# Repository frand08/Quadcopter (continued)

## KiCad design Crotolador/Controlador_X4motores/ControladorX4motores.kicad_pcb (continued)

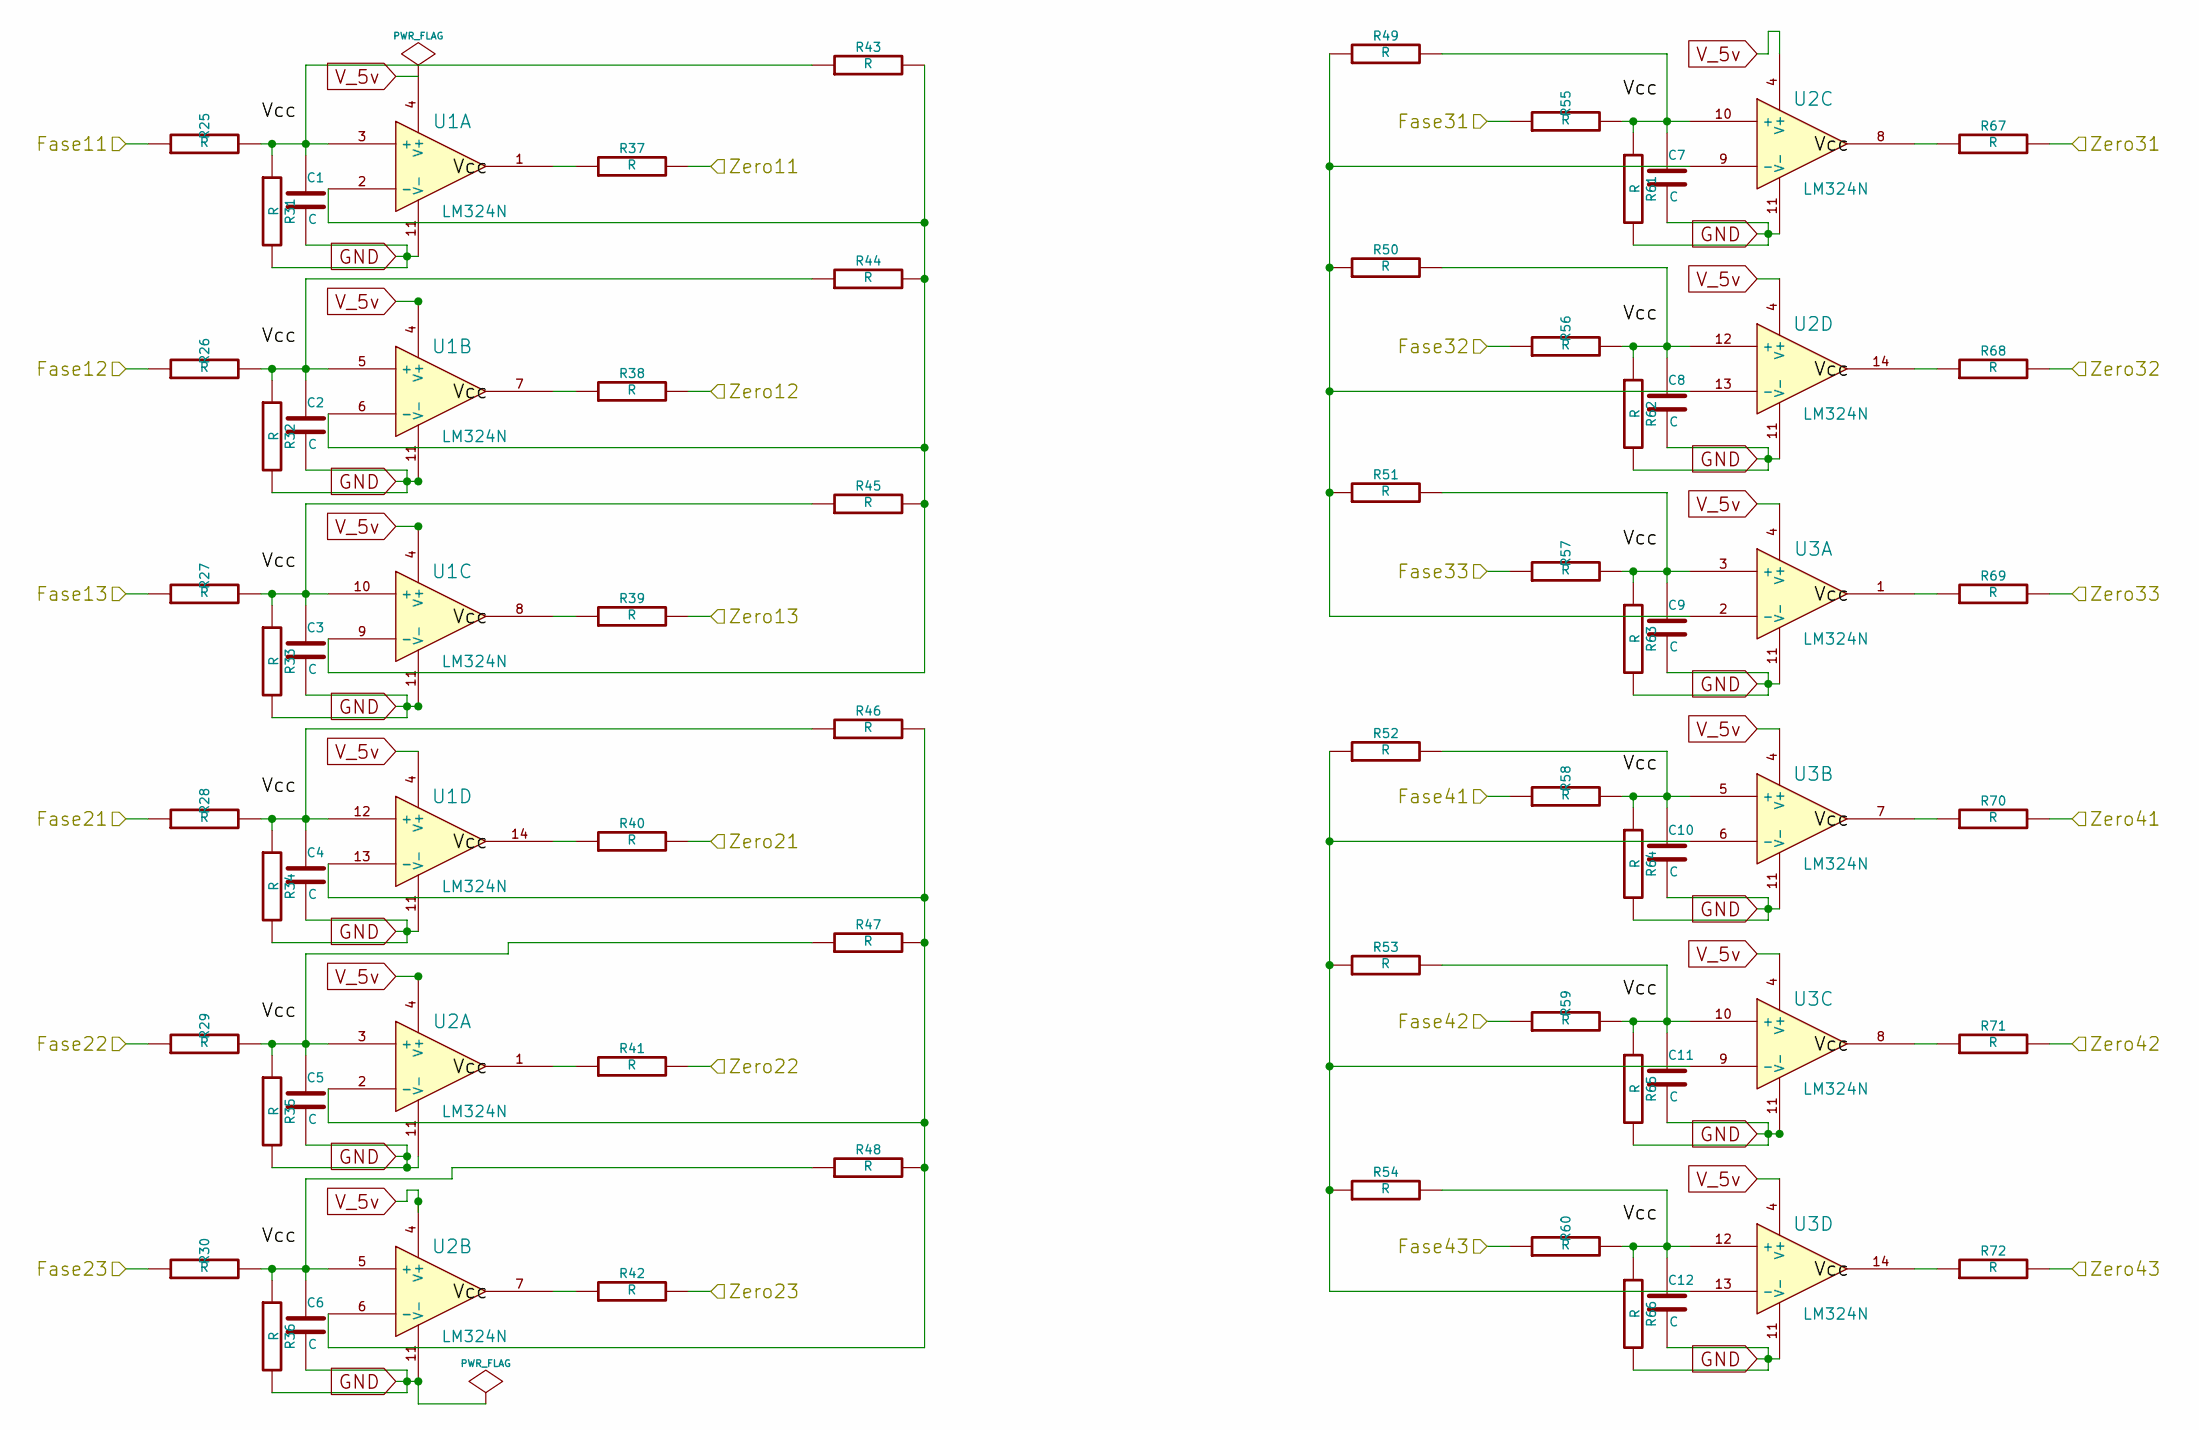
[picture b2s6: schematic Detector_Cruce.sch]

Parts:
C1, C2, C3, C4, C5, C6, C7, C8, C9, C10, C11, C12: C
R25, R26, R27, R28, R29, R30, R31, R32, R33, R34, R35, R36, R37, R38, R39, R40, R41, R42, R43, R44, R45, R46, R47, R48, R49, R50, R51, R52, R53, R54, R55, R56, R57, R58, R59, R60, R61, R62, R63, R64, R65, R66, R67, R68, R69, R70, R71, R72: R
U1, U2, U3: LM324N

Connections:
/Detector_Cruce/Fase12: R26.1; also elsewhere on the board
/Detector_Cruce/Fase13: R27.1; also elsewhere on the board
/Detector_Cruce/Fase23: R30.1; also elsewhere on the board
/Detector_Cruce/Zero11: R37.2; also elsewhere on the board
/Detector_Cruce/Zero12: R38.2; also elsewhere on the board
/Detector_Cruce/Zero13: R39.2; also elsewhere on the board
/Detector_Cruce/Zero21: R40.2; also elsewhere on the board
/Detector_Cruce/Zero22: R41.2; also elsewhere on the board
/Detector_Cruce/Zero23: R42.2; also elsewhere on the board
/Detector_Cruce/Zero31: R67.2; also elsewhere on the board
/Detector_Cruce/Zero32: R68.2; also elsewhere on the board
/Detector_Cruce/Zero33: R69.2; also elsewhere on the board
/Detector_Cruce/Zero41: R70.2; also elsewhere on the board
/Detector_Cruce/Zero42: R71.2; also elsewhere on the board
/Detector_Cruce/Zero43: R72.2; also elsewhere on the board
/MOSFET_Potencia1/Fase1: R25.1; also elsewhere on the board
/MOSFET_Potencia2/Fase1: R28.1; also elsewhere on the board
/MOSFET_Potencia2/Fase2: R29.1; also elsewhere on the board
/MOSFET_Potencia3/Fase1: R55.1; also elsewhere on the board
/MOSFET_Potencia3/Fase2: R56.1; also elsewhere on the board
/MOSFET_Potencia3/Fase3: R57.1; also elsewhere on the board
/MOSFET_Potencia4/Fase1: R58.1; also elsewhere on the board
/MOSFET_Potencia4/Fase2: R59.1; also elsewhere on the board
/MOSFET_Potencia4/Fase3: R60.1; also elsewhere on the board
GND: C1.2, C2.2, C3.2, C4.2, C5.2, C6.2, C7.2, C8.2, C9.2, C10.2, C11.2, C12.2, R31.2, R32.2, R33.2, R34.2, R35.2, R36.2, R61.2, R62.2, R63.2, R64.2, R65.2, R66.2, U1.11 (V-), U2.11 (V-), U3.11 (V-); also elsewhere on the board
unnamed: R71.1, U3.8
unnamed: R72.1, U3.14
unnamed: C12.1, R54.2, R60.2, R66.1, U3.12 (+)
unnamed: R52.1, R53.1, R54.1, U3.6 (-), U3.9 (-), U3.13 (-)
unnamed: R70.1, U3.7
unnamed: C1.1, R25.2, R31.1, R43.1, U1.3 (+)
unnamed: R43.2, R44.2, R45.2, U1.2 (-), U1.6 (-), U1.9 (-)
unnamed: R40.1, U1.14
unnamed: R46.2, R47.2, R48.2, U1.13 (-), U2.2 (-), U2.6 (-)
unnamed: R41.1, U2.1
unnamed: R38.1, U1.7
unnamed: R39.1, U1.8
unnamed: R68.1, U2.14
unnamed: R69.1, U3.1
unnamed: R42.1, U2.7
unnamed: R67.1, U2.8
unnamed: R49.1, R50.1, R51.1, U2.9 (-), U2.13 (-), U3.2 (-)
unnamed: C4.1, R28.2, R34.1, R46.1, U1.12 (+)
unnamed: C5.1, R29.2, R35.1, R47.1, U2.3 (+)
unnamed: C6.1, R30.2, R36.1, R48.1, U2.5 (+)
unnamed: R37.1, U1.1
unnamed: C2.1, R26.2, R32.1, R44.1, U1.5 (+)
unnamed: C3.1, R27.2, R33.1, R45.1, U1.10 (+)
unnamed: C10.1, R52.2, R58.2, R64.1, U3.5 (+)
unnamed: C11.1, R53.2, R59.2, R65.1, U3.10 (+)
unnamed: C7.1, R49.2, R55.2, R61.1, U2.10 (+)
unnamed: C8.1, R50.2, R56.2, R62.1, U2.12 (+)
unnamed: C9.1, R51.2, R57.2, R63.1, U3.3 (+)
V_5v: U1.4 (V+), U2.4 (V+), U3.4 (V+); also elsewhere on the board

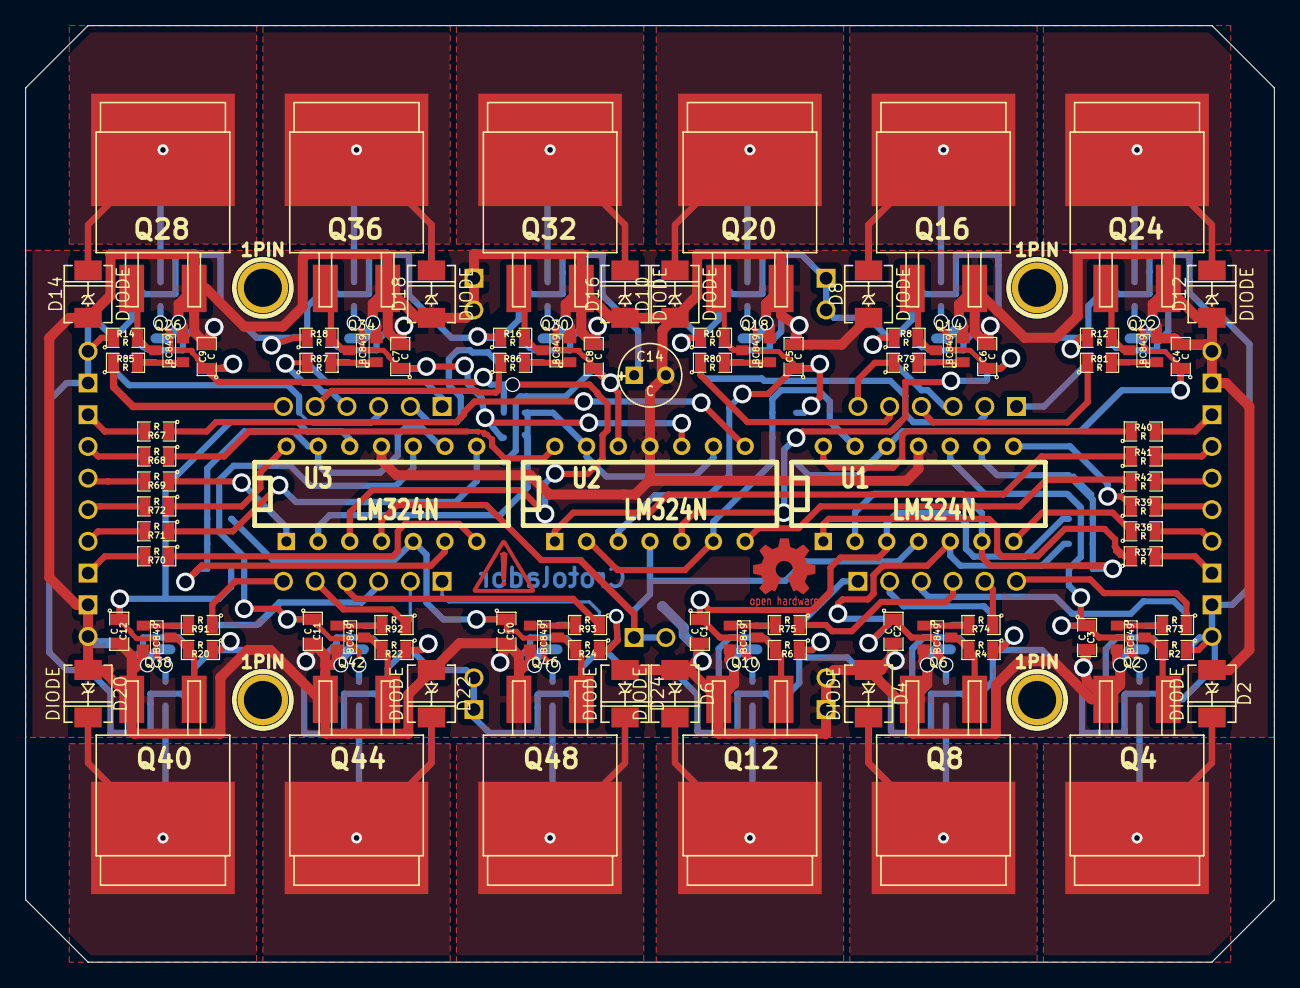
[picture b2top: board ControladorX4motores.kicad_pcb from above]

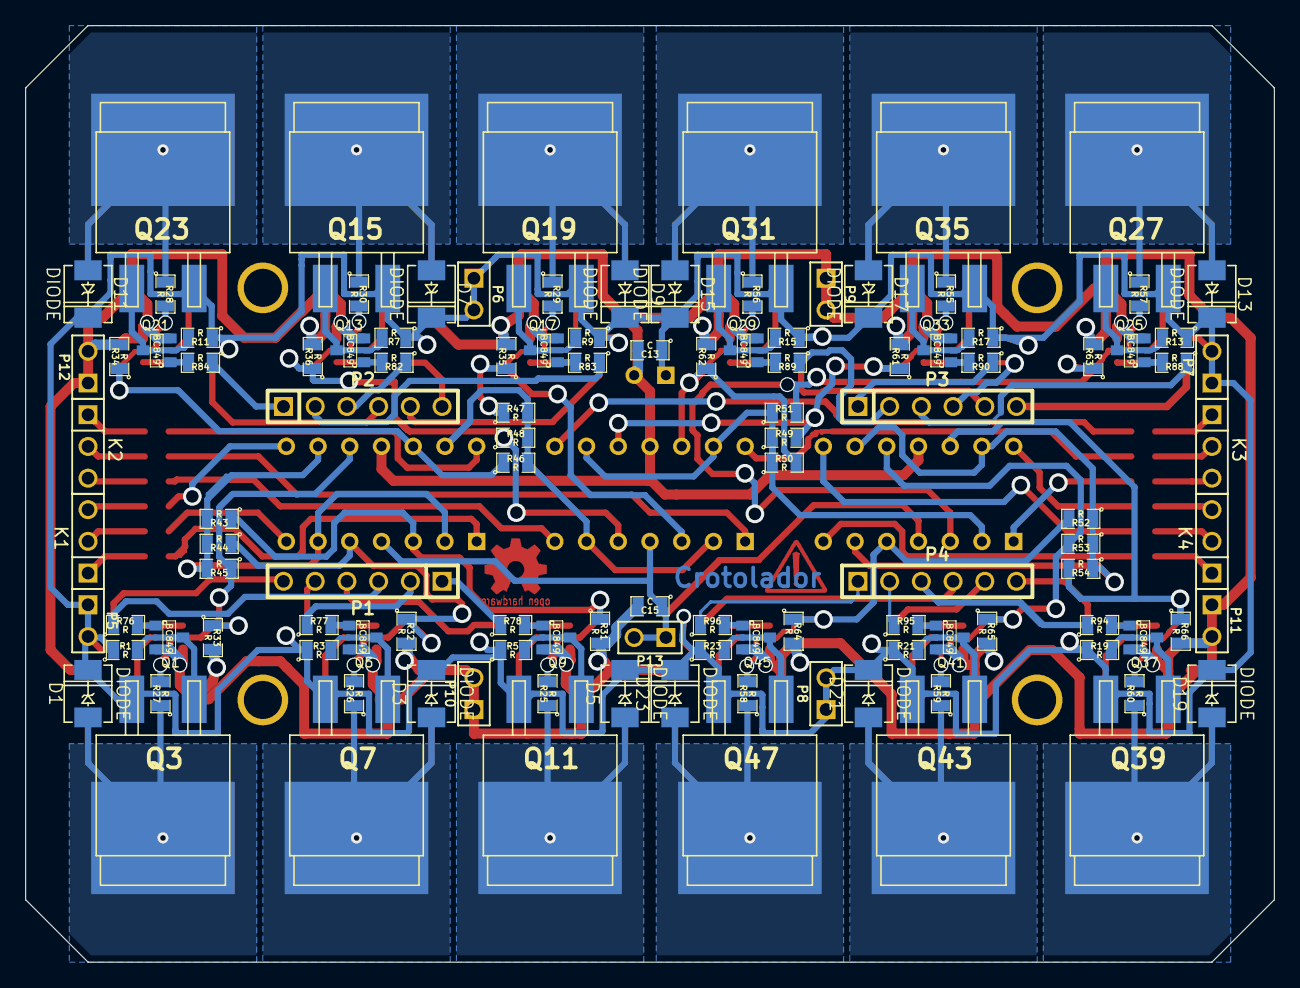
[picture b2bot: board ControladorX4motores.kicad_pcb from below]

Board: 2 copper layers, 100.0 x 75.0 mm, 207 parts (115 on the bottom side), 127 nets.

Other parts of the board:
1PIN, 1PIN#2, 1PIN#3, 1PIN#4: P***; 1pin

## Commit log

2015-09-02 Carpetas y archivos
2015-09-05 El croto para un motor diseñado casi terminado
